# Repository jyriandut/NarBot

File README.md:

# NarBot

NarBot is an experimental SMARS-style robot workspace. It currently contains
PlatformIO firmware for ESP32 camera/control nodes plus a KiCad PCB project.

The active firmware work is focused on getting reliable ESP32 camera streams,
basic Wi-Fi setup, and simple robot-control building blocks working before
adding a larger autonomous control stack.

## Projects

### `NarbotESP`

Minimal dual-camera firmware for two Seeed Studio XIAO ESP32S3 Sense boards.
The same codebase builds in two modes:

- `main_esp`: starts the `SMARS_MAIN` access point at `192.168.4.1`, serves the
  dashboard, and streams its local camera.
- `front_esp`: joins `SMARS_MAIN` as a station, tries to use static IP
  `192.168.4.10`, and serves its own camera stream.

Main endpoints:

- `http://192.168.4.1/` - dashboard hosted by the main ESP
- `/status` - JSON status
- `/jpg` - single JPEG frame
- `/stream` - MJPEG stream

Default Wi-Fi credentials used by the prototype:

- SSID: `SMARS_MAIN`
- Password: `smars1234`

Build and upload:

```sh
cd NarbotESP
make compile
make upload_main
make upload_front
make monitor
```

Equivalent PlatformIO commands:

```sh
pio run -e main_esp -t upload
pio run -e front_esp -t upload
pio device monitor
```

### `CameraDriver`

Experimental all-in-one XIAO ESP32S3 Sense firmware. This project currently
contains motor-control, camera capture/streaming, setup AP, simple web UI,
serial console, headlight/status LED behavior, and color-sensor code.

Hardware assumptions in the current firmware include:

- Seeed Studio XIAO ESP32S3 Sense with camera
- DFRobot TB6612FNG motor driver
- TCS34725-compatible color sensor at I2C address `0x29`

Setup AP used by the prototype:

- SSID: `CameraDriver-Setup`
- Password: `smars1234`

Build and upload:

```sh
cd CameraDriver
make compile
make upload
make monitor
```

### `NarbotPCB`

KiCad PCB project for the robot electronics.

Commit these files:

- `*.kicad_pro`
- `*.kicad_sch`
- `*.kicad_pcb`

Local KiCad backups and project-local state are ignored by
`NarbotPCB/.gitignore`.

### `ColorCalibration`

Placeholder/calibration workspace. At the moment only generated PlatformIO
output was present, so `.pio/` is ignored there.

## Repository Layout

```text
.
├── CameraDriver/      # Experimental ESP32 camera + motor driver firmware
├── ColorCalibration/  # Calibration workspace
├── NarbotESP/         # Two-ESP camera streaming firmware
├── NarbotPCB/         # KiCad board project
└── README.md
```

## Requirements

- PlatformIO CLI (`pio`)
- USB serial access to the ESP32 boards
- KiCad for the PCB project

The firmware targets ESP32 boards through PlatformIO's `espressif32` platform
and uses the Arduino framework.

## Git Notes

Each project has its own `.gitignore` for generated files. Build output,
downloaded PlatformIO dependencies, clangd caches, notebook scratch files,
macOS metadata, and KiCad backups should stay uncommitted.

Useful status check:

```sh
git status --short --untracked-files=all
```

## Current Milestone

The main firmware milestone is:

1. Main ESP starts the `SMARS_MAIN` access point.
2. Main dashboard opens at `http://192.168.4.1/`.
3. Main ESP camera stream is visible.
4. Front ESP connects to the main AP at `192.168.4.10`.
5. Front ESP stream appears in the main dashboard.

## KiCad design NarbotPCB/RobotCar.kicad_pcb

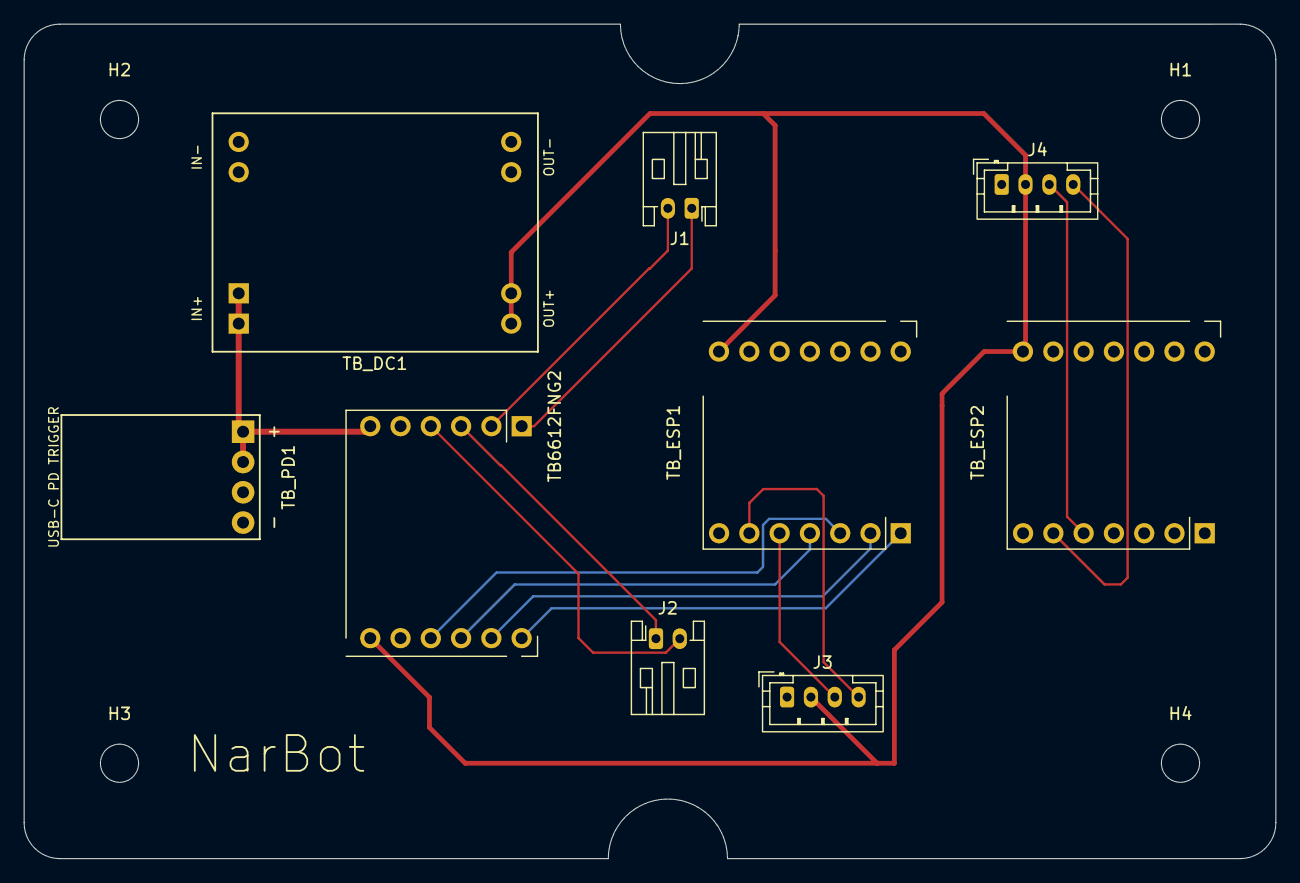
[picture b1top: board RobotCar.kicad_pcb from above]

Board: 2 copper layers, 105.0 x 70.0 mm, 13 parts (0 on the bottom side), 15 nets.

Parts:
H1, H2, H3, H4: MountingHole; MountingHole_3.2mm_M3
J1: Motor_1_Conn; JST_PH_S2B-PH-K_1x02_P2.00mm_Horizontal
J2: Motor_2_Conn; JST_PH_S2B-PH-K_1x02_P2.00mm_Horizontal
J3: ColorI2C; JST_PH_B4B-PH-K_1x04_P2.00mm_Vertical
J4: DistanceI2C; JST_PH_B4B-PH-K_1x04_P2.00mm_Vertical
TB6612FNG2: Motor_DF_Robot_Through_Hole
TB_DC1: DFRobot_DFR1015_Socket_Carrier_2.54mm
TB_ESP1, TB_ESP2: Seeed_XIAO_Sense_2x07_SMD_Socket_12.70mm
TB_PD1: OKY3404_PDC004_PD_Trigger_Socket_1x04

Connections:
+5V: J3.2, J4.2, TB6612FNG2.12 (VCC), TB_DC1.3 (OUT+), TB_ESP1.14 (5V), TB_ESP2.14 (5V)
+12V: TB6612FNG2.6 (VM), TB_DC1.1 (IN+), TB_PD1.1 (OUT+)
/DIR1: TB6612FNG2.7 (DIR1), TB_ESP1.1 (D0)
/DIR2: TB6612FNG2.10 (DIR2), TB_ESP1.3 (D2)
/PWM1: TB6612FNG2.8 (PWM1), TB_ESP1.2 (D1)
/PWM2: TB6612FNG2.9 (PWM2), TB_ESP1.4 (D3)
/SCL_1: J3.4, TB_ESP1.6 (SCL/D5)
/SCL_2: J4.4, TB_ESP2.6 (SCL/D5)
/SDA_1: J3.3, TB_ESP1.5 (SDA/D4)
/SDA_2: J4.3, TB_ESP2.5 (SDA/D4)
GND: J3.1, J4.1, TB6612FNG2.5 (GND), TB6612FNG2.11 (GND), TB_DC1.2 (IN-), TB_DC1.4 (OUT-), TB_ESP1.13 (GND), TB_ESP2.13 (GND), TB_PD1.2 (OUT-)
unnamed: J1.1, TB6612FNG2.1 (M1+)
unnamed: J1.2, TB6612FNG2.2 (M1-)
unnamed: J2.1, TB6612FNG2.3 (M2+)
unnamed: J2.2, TB6612FNG2.4 (M2-)

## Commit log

2026-06-24 Init
2026-06-24 Add verstapostid
2026-06-24 Add cad
2026-06-26 Fix design
2026-06-26 Motor dirver
2026-06-26 Update ESP logic
2026-06-26 Add analysis, docs, and extra code
2026-06-26 Add qr_reader_xiao from sumo-robot-project
2026-06-28 Fix kere2 cutouts
2026-06-29 Update KiCad project
